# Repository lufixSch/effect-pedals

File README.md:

# effect-pedals
Circuits and PCB designs for audio effect pedals

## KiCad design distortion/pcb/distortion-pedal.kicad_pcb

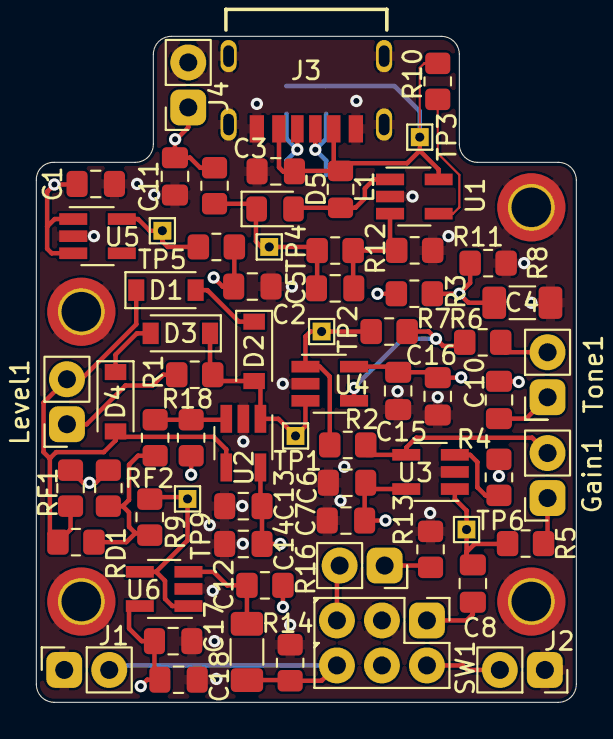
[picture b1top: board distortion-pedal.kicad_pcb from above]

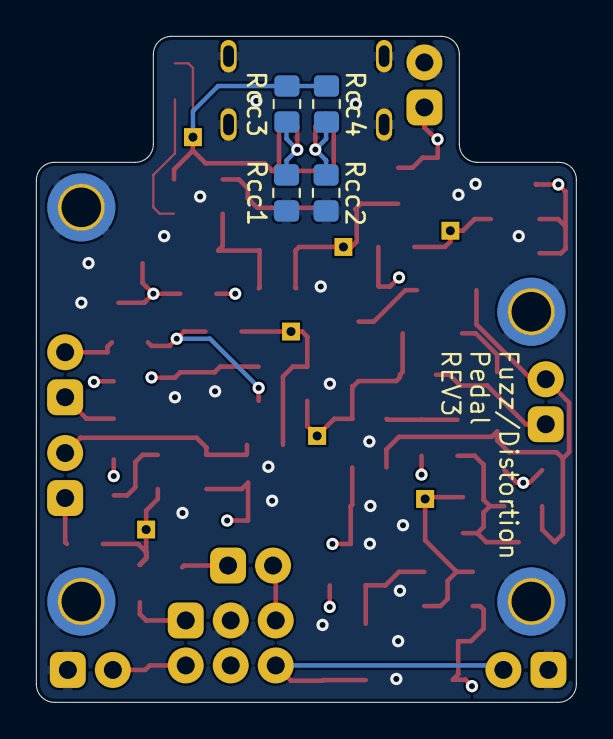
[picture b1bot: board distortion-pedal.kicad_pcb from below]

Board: 4 copper layers, 30.0 x 37.0 mm, 75 parts (4 on the bottom side), 34 nets.

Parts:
C1, C2: 0.47uF; C_0805_2012Metric_Pad1.18x1.45mm_HandSolder
C3: 2.2uF; C_0805_2012Metric_Pad1.18x1.45mm_HandSolder
C4: 33uF; C_1206_3216Metric_Pad1.33x1.80mm_HandSolder
C5: 330pF; C_0805_2012Metric_Pad1.18x1.45mm_HandSolder
C6, C13, C15, C17: 100nF; C_0805_2012Metric_Pad1.18x1.45mm_HandSolder
C7, C10, C14, C16, C18: 10uF; C_0805_2012Metric_Pad1.18x1.45mm_HandSolder
C8: C; C_0805_2012Metric_Pad1.18x1.45mm_HandSolder
C11: 4.7uF; C_0805_2012Metric_Pad1.18x1.45mm_HandSolder
C12: 22uF; C_1206_3216Metric_Pad1.33x1.80mm_HandSolder
D1, D2, D3, D4: 1N4148; D_SOD-123
D5: SD0805S020S1R0; D_0805_2012Metric_Pad1.15x1.40mm_HandSolder
D6: LED; led_wired_1_pin
Gain1: 10k; potentiometer_wired_23_connected
H1, H2, H3, H4: MountingHole_Pad; MountingHole_2.2mm_M2_DIN965_Pad_TopBottom
J1, J2: AudioJack2_Ground; audio_jack_wired
J3: USB4125-GF-A-0190; GCT_USB4125-GF-A-0190_REVA2
J4: Barrel_Jack; barrel_jack_wired
JP1, JP2: Jumper_2_Open; R_0805_2012Metric_Pad1.20x1.40mm_HandSolder
JPF1: Jumper_2_Open; R_0805_2012Metric_Pad1.20x1.40mm_HandSolder
L1: 10uH; L_0805_2012Metric_Pad1.15x1.40mm_HandSolder
Level1: R; potentiometer_wired_23_connected
R1, R2, R4, R5, R6, R7, R9, R18: R; R_0805_2012Metric_Pad1.20x1.40mm_HandSolder
R3, R8: 10k; R_0805_2012Metric_Pad1.20x1.40mm_HandSolder
R10: 100k; R_0805_2012Metric_Pad1.20x1.40mm_HandSolder
R11: 13k; R_0805_2012Metric_Pad1.20x1.40mm_HandSolder
R12: 82k; R_0805_2012Metric_Pad1.20x1.40mm_HandSolder
R13: 300; R_0805_2012Metric_Pad1.20x1.40mm_HandSolder
R14, R16: 510k; R_0805_2012Metric_Pad1.20x1.40mm_HandSolder
RD1: R; R_0805_2012Metric_Pad1.20x1.40mm_HandSolder
RF1, RF2: R; R_0805_2012Metric_Pad1.20x1.40mm_HandSolder
Rcc1, Rcc2, Rcc3, Rcc4: 5.1k; R_0805_2012Metric_Pad1.20x1.40mm_HandSolder
SW1: SW_DPDT_x2; switch_wired
TP1, TP2, TP3, TP4, TP5, TP6, TP9: TestPoint; TestPoint_THTPad_1.0x1.0mm_Drill0.5mm
Tone1: R; potentiometer_wired_12_connected
U1: LMR62014XMF-NOPB; SOT-23-5_HandSoldering
U2, U3, U4, U6: TL081H; SOT-23-5_HandSoldering
U5: TLV767; SOT-23-5_HandSoldering

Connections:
+4V: C4.1, C10.2, R3.1, R4.2, R8.2, R16.2, R18.2, RF1.2, RF2.1
+5V: C3.1, J3.A9 (VBUS), J3.B9 (VBUS), L1.1, R10.1, Rcc3.1, Rcc4.1, TP3.1, U1.5 (VIN)
+8V: C2.1, C6.1, C7.1, C13.1, C14.1, C15.1, C16.1, C17.1, C18.1, JP2.2 (B), R3.2, SW1.4, U2.5 (V+), U3.5 (V+), U4.5 (V+), U6.5 (V+)
+9V: C1.1, C11.1, J4.1, JP1.2 (B), U5.1 (IN), U5.3 (EN)
GND: C1.2, C2.2, C3.2, C4.2, C6.2, C7.2, C11.2, C13.2, C14.2, C15.2, C16.2, C17.2, C18.2, H1.1, H2.1, H3.1, H4.1, J1.1, J2.1, J3.A12 (GND), J3.B12 (GND), J3.S1 (SHIELD), J3.S2 (SHIELD), J3.S3 (SHIELD), J3.S4 (SHIELD), J4.2, R8.1, R11.2, R13.2, R14.2, Rcc1.2, Rcc2.2, SW1.6, U1.2 (GND), U2.2 (V-), U3.2 (V-), U4.2 (V-), U5.2 (GND), U6.2 (V-)
unnamed: C5.1, R11.1, R12.1, U1.3 (FB)
unnamed: C5.2, D5.1 (K), JP1.1 (A), R12.2, TP4.1
unnamed: C8.1, R5.1, TP6.1, U3.1 (OUT)
unnamed: C10.1, Tone1.1, Tone1.2
unnamed: C12.2, R16.1, U6.3 (+IN)
unnamed: D1.1 (K), D4.2 (A), Level1.2, Level1.3, RD1.2, RF1.1, U2.4 (-IN)
unnamed: D1.2 (A), D2.1 (K)
unnamed: D2.2 (A), D3.1 (K), R1.2, TP1.1, U2.1 (OUT), U4.3 (+IN)
unnamed: D3.2 (A), D4.1 (K)
unnamed: D5.2 (A), L1.2, U1.1 (SW)
unnamed: D6.1 (K), R13.1
unnamed: D6.2 (A), SW1.5
unnamed: Gain1.1, R5.2
unnamed: Gain1.2, Gain1.3, R2.1, U3.4 (-IN)
unnamed: J2.2, SW1.2
unnamed: J3.A5 (CC1), Rcc1.1, Rcc3.2
unnamed: J3.B5 (CC2), Rcc2.1, Rcc4.2
unnamed: JP2.1 (A), TP5.1, U5.5 (OUT)
unnamed: JPF1.1 (A), R9.1, RD1.1, RF2.2
unnamed: JPF1.2 (B), R18.1, U2.3 (+IN)
unnamed: Level1.1, R1.1
unnamed: R4.1, U3.3 (+IN)
unnamed: R6.1, Tone1.3
unnamed: R6.2, R7.1, U4.4 (-IN)
unnamed: R10.2, U1.4 (SHDN)
audio_in: C12.1, J1.2, R14.1, SW1.3
effect_in: R9.2, TP9.1, U6.1 (OUT), U6.4 (-IN)
effect_out: R2.2, R7.2, TP2.1, U4.1 (OUT)
gain_out: C8.2, SW1.1

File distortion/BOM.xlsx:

Designator | Package | Distortion - Model/Value | Fuzz - Model/Value
U1 | SOT-23-5 | LMR62014XMF-NOPB | LMR62014XMF-NOPB
U2 | SOT-23-5 | TL081H | TL081H
U3 | SOT-23-5 | TL081H | TL081H
U4 | SOT-23-5 | TL081H | TL081H
U5 | SOT-23-5 | TLV767 | TLV767
U6 | SOT-23-5 | TL081H | TL081H
D1 | SOD-123 | 1N4148 | 1N4148
D2 | SOD-123 | 1N4148 | 1N4148
D3 | SOD-123 | 1N4148 | 1N4148
D4 | SOD-123 | 1N4148 | 1N4148
D5 | 0805-2012 | SD0805S020S1R0 | SD0805S020S1R0
D6 | PinHeader_1x2 | Red LED | Red LED
J1 | PinHeader_1x2 | 6.3mm Audio Jack | 6.3mm Audio Jack
J2 | PinHeader_1x2 | 6.3mm Audio Jack | 6.3mm Audio Jack
J3 | GCT_USB4125-GF-A-0190_REVA2 | USB4125-GF-A-0190 | USB4125-GF-A-0190
J4 | PinHeader_1x2 | 9V Barrel Jack | 9V Barrel Jack
JP1 | R_0805-2012 | 0Ω | 0Ω
JP2 | R_0805-2012 | 0Ω | 0Ω
JPF1 | R_0805-2012 | 0Ω | -
SW1 | PinHeader_2x3 | 6P DPDT Foot Switch | 6P DPDT Foot Switch
L1 | Abracon ASPI 3012S | 10uH | 10uH
Rcc1 | R_0805-2012 | 5.1k | 5.1k
Rcc2 | R_0805-2012 | 5.1k | 5.1k
Rcc3 | R_0805-2012 | 5.1k | 5.1k
Rcc4 | R_0805-2012 | 5.1k | 5.1k
Level1 | PinHeader_1x3 | 10k | 50k
Tone1 | PinHeader_1x3 | 10k | 10k
Gain1 | PinHeader_1x3 | 10k | 10k
R1 | R_0805-2012 | 100Ω | 1k
R2 | R_0805-2012 | 5.1k | 5.1k
R3 | R_0805-2012 | 10k | 10k
R4 | R_0805-2012 | 100k | 100k
R5 | R_0805-2012 | 0Ω | 0Ω
R6 | R_0805-2012 | 100Ω | 100Ω
R7 | R_0805-2012 | 2k | 2k
R8 | R_0805-2012 | 10k | 10k
R9 | R_0805-2012 | 0Ω | 100k
R10 | R_0805-2012 | 100k | 100k
R11 | R_0805-2012 | 13k | 13k
R12 | R_0805-2012 | 82k | 82k
R13 | R_0805-2012 | 300Ω | 300Ω
R14 | R_0805-2012 | 510k | 510k
R16 | R_0805-2012 | 510k | 510k
R18 | R_0805-2012 | 100k | 100k
RD1 | R_0805-2012 | 100Ω | -
RF1 | R_0805-2012 | - | 1k
RF2 | R_0805-2012 | - | 100k
C1 | C_0805-2012 | 470nF | 470nF
C2 | C_0805-2012 | 470nF | 470nF
C3 | C_0805-2012 | 2.2uF | 2.2uF
C4 | C_1206-3216 | 22uF | 22uF
C5 | C_0805-2012 | 330pF | 330pF
C6 | C_0805-2012 | 100nF | 100nF
C7 | C_0805-2012 | 10uF | 10uF
C8 | C_0805-2012 | 10uF | 10uF
C10 | C_0805-2012 | 20nF | 20nF
C11 | C_0805-2012 | 4.7uF | 4.7uF
C12 | C_1206-3216 | 22uF | 22uF
C13 | C_0805-2012 | 100nF | 100nF
C14 | C_0805-2012 | 10uF | 10uF
C15 | C_0805-2012 | 100nF | 100nF
C16 | C_0805-2012 | 10uF | 10uF
C17 | C_0805-2012 | 100nF | 100nF
C18 | C_0805-2012 | 10uF | 10uF

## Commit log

2022-10-18 INIT
2022-10-23 add basic distortion pedal
2022-10-24 add circuit dimensioning
2022-10-25 add BOM, rework dimensioning
2022-11-06 rework distortion circuit and simulations
2022-11-06 remove simulation tmp data
2022-11-07 create gerber files, update BOM for REV2
2022-12-13 distortion rev 3
2022-12-20 WIP fix project error
2022-12-20 distortion pedal REV3 Gerber files
2022-12-20 add low pass treble simulation
2022-12-20 add reverb circuit
2022-12-20 rework global circuits
2022-12-20 fix project error
2023-01-03 minor circuit rework for better use with multiple projects
2023-01-04 update BOM
2023-01-04 add models for spring reverb
